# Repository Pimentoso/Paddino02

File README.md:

# Paddino02

10-keys DIY mechanical macropad/gamepad. Features staggered columns, 2 thumb keys, symmetric PCB (you can build right-handed and left-handed versions with the same PCB). Intended to use with [QMK firmware](https://qmk.fm).

### What you need

- a Paddino02 PCB. I suggest ordering it at [JLCPCB](http://jlcpcb.com), you can get 5 PCBs for just $2. Instructions for ordering below.
- an Arduino Pro Micro. Aliexpress link https://www.aliexpress.com/item/32849563958.html
- x10 1N4148 diodes. Aliexpress link https://www.aliexpress.com/item/32804799676.html
- x10 mechanical keyboard switches of your choice. Aliexpress link https://www.aliexpress.com/item/32679823499.html
- x10 keycaps. Aliexpress link https://www.aliexpress.com/item/32850729893.html
- Access to a soldering iron
- Access to a 3d printer
- x5 small M2 screws, 5mm long or so.
- Optional adhesive rubber feets.

### Building the pad

- solder the 10 diodes. The black heads of the diodes must be oriented towards the square-marked holes in the PCB.
- solder the header pins.
- solder the Pro Micro. Either you are building the right or left version, the USB port side must face the PCB.
- cut away the excess of the header pins using pliers/nippers.
- print a plate and snap the switches into the holes.
- insert the switches pins into the PCB and solder them in.
- flash the firmware (see next section).
- print a case and screw the two parts together.

*Some PCBs. The white ones are from the first revision, they're just in the pic for show.*

*Pro Micro soldered with header pins. The pins are too long and need to be snipped.*

*Plate with blue switches snapped in place.*

*PCB joined with plate.*

*Right and left versions.*

*Finished pads (first revision)*

*Finished pad (second revision). Compared to the first revision, the screw holes are hidden between the switches.*

### Flashing the firmware

The firmware folder contains the keymap .json files and firmware .hex files for both the right and left handed versions. 

#### Editing the keymap

The provided keymap files are very basic, and the second layer is empty. So some customization is recommended. 

To edit the keys, you have to load the .json file into https://kbfirmware.com/, configure the keys as you like, and compile a .hex file directly from the site. You can then flash the .hex file on the pad using avrdude.

#### Flashing

The easiest way is to install [QMK Toolbox](https://github.com/qmk/qmk_toolbox/releases)

Connect your pad to USB, enter programming mode, select the .hex file into QMK Toolbox, and flash.

To enter programming mode, use the hole on the bottom of the case. You can stick a bent clip/screwdriver into it to short the RESET and GROUND pins of the Pro Micro. (There are actually 2 holes, because in the right-handed version the Pro Micro is flipped and the pins are on the other side)

#### Keyboard Layout Editor links

- http://www.keyboard-layout-editor.com/#/gists/999c722bfd1635b06a1ac5182787ecb8 (left handed version)
- http://www.keyboard-layout-editor.com/#/gists/7b56ab607e70723b96f63006d65ebe46 (right handed version)

## Ordering the PCB

Head over to https://jlcpcb.com/quote and upload the gerber.zip file, located inside the kicad/gerber folder. The default options are good (you can change the color for swag). Just make sure PCB Thickness is set to 1.6. 

Since the PCB is smaller than 100mm, the cost will be $2 for 5 of them, and shipping will be free if it's your first order.

## License

This project is licensed under the GPLv3 License - see the [LICENSE.md](LICENSE.md) file for details

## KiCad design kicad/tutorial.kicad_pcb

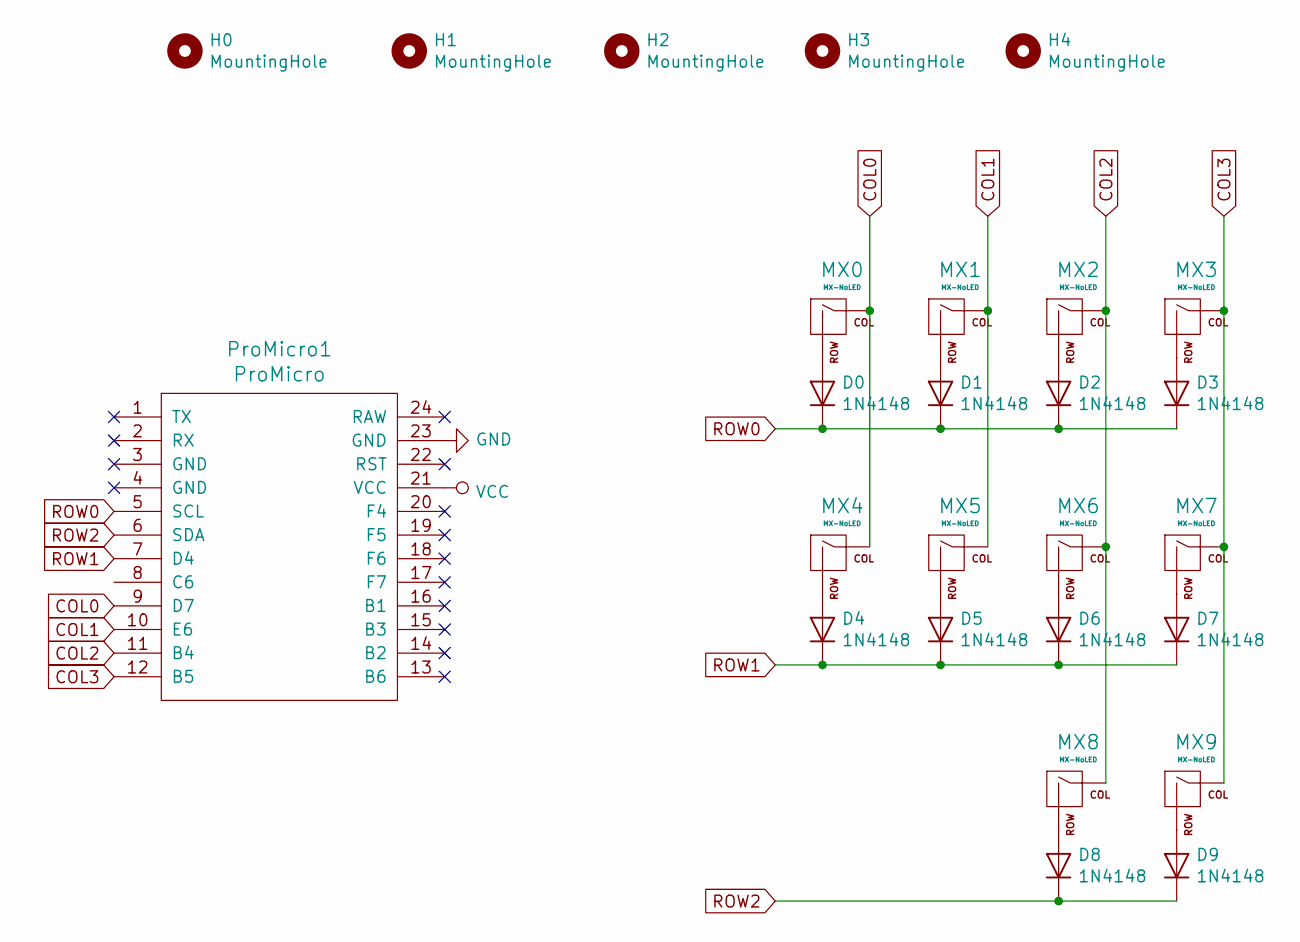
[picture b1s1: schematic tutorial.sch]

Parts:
D0, D1, D2, D3, D4, D5, D6, D7, D8, D9: 1N4148; D_DO-35_SOD27_P7.62mm_Horizontal
H0, H1, H2, H3, H4: MountingHole; MountingHole_2.2mm_M2
MX0, MX1, MX2, MX3, MX4, MX5, MX6, MX7, MX8, MX9: MX-NoLED; MX_reversible
ProMicro1: ProMicro; ArduinoProMicro

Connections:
COL0: MX0.1 (COL), MX4.1 (COL), ProMicro1.9 (D7)
COL1: MX1.1 (COL), MX5.1 (COL), ProMicro1.10 (E6)
COL2: MX2.1 (COL), MX6.1 (COL), MX8.1 (COL), ProMicro1.11 (B4)
COL3: MX3.1 (COL), MX7.1 (COL), MX9.1 (COL), ProMicro1.12 (B5)
GND: ProMicro1.23 (GND)
unnamed: D0.2 (A), MX0.2 (ROW)
unnamed: D1.2 (A), MX1.2 (ROW)
unnamed: D2.2 (A), MX2.2 (ROW)
unnamed: D3.2 (A), MX3.2 (ROW)
unnamed: D4.2 (A), MX4.2 (ROW)
unnamed: D5.2 (A), MX5.2 (ROW)
unnamed: D6.2 (A), MX6.2 (ROW)
unnamed: D7.2 (A), MX7.2 (ROW)
unnamed: D8.2 (A), MX8.2 (ROW)
unnamed: D9.2 (A), MX9.2 (ROW)
ROW0: D0.1 (K), D1.1 (K), D2.1 (K), D3.1 (K), ProMicro1.5 (SCL)
ROW1: D4.1 (K), D5.1 (K), D6.1 (K), D7.1 (K), ProMicro1.7 (D4)
ROW2: D8.1 (K), D9.1 (K), ProMicro1.6 (SDA)
VCC: ProMicro1.21 (VCC)

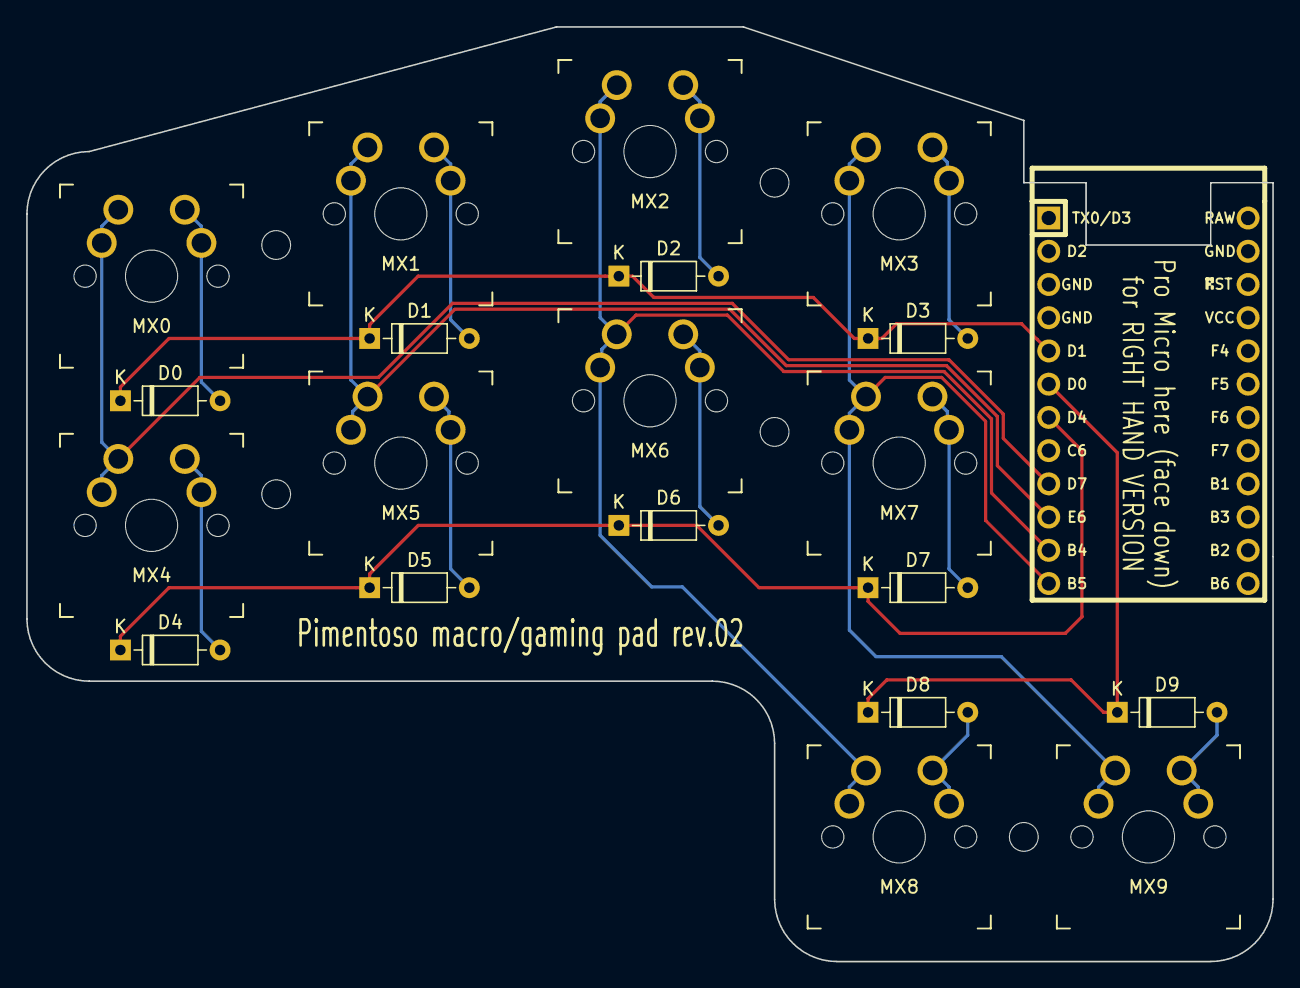
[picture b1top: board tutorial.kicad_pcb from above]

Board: 2 copper layers, 95.3 x 71.4 mm, 26 parts (0 on the bottom side), 17 nets.

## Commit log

2019-07-23 move files from other repo
2019-07-23 finalized pcb, added both kbfirmware json files
2019-07-24 readme and pics
2019-07-24 readme
2019-07-25 edit firmware files
2019-07-26 readme and new rendering
2019-07-26 new case stl
2019-08-01 fix lib broken links
2019-12-24 fix right version pins
